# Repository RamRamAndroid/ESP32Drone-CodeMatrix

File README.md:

## Introduction Of CodeMatrix ESP32 Drone

CodeMatrix ESP32 Drone is a compact, WiFi-controlled drone based on the ESP32-S3 microcontroller. Designed for hobbyists, makers, and engineers, CodeMatrix ESP32 Drone offers a simple yet powerful platform for drone experimentation and development. It is an open-hardware project, making it easy to modify and expand.

Whether you’re new to drones or an experienced developer looking to create custom flight applications, LiteWing provides an accessible and affordable way to explore drone technology. Unlike traditional drones that require proprietary controllers, CodeMatrix ESP32 Drone connects to your smartphone, allowing for an intuitive flying experience without additional hardware.

The firmware on CodeMatrix ESP32 Drone supports Crazyflie cfclient and cflib, meaning you can program and control your drone using Python and add more features like height hold, position hold, gesture control, and more.

The latest version includes more GPIO pins, sensor mounts, LED indicators to make it easier to tinker with and program. The PCB frame design keeps it lightweight while reducing costs, making it one of the most affordable DIY drones available.

### Note:- The Files Related To The Drone Are In The Folder Named "Drone"

## Introduction Of CodeMatrix ESP32 Drone Positioning Module

The ESP32 Drone Positioning Module is a plug-and-play optical flow and ToF-based stabilization add-on designed for indoor and GPS-denied flight. Featuring the PMW3901 optical flow sensor for precise X/Y position tracking and the VL53L1X Time-of-Flight sensor for accurate height measurement, this module enables stable height hold and position hold performance. Ideal for DIY drones, autonomous flight experiments, and educational robotics projects.

This module transforms your CodeMatrix ESP32 Drone and Litewing Drone into a fully-equipped autonomous flight platform by adding critical sensor capabilities: precision ToF height measurement, optical motion tracking, and visual status feedback. All connected through a 24-pin connector, eliminating complex wiring while maintaining robust electrical connections suitable for flight operations.

This add-on module is completely compatible with the CodeMatrix ESP32 Drone and LiteWing Drones and consists of the VL53L1x ToF sensor and PMW3901MB optical flow sensor for height hold and position hold, respectively. Apart from this, the module also has 4 Neopixel LEDs that can be programmed to indicate flight status or for visual appeal.

Important: By default, only the ToF sensor, Optical Flow sensor, and Neopixel LEDs will be soldered on the module. The brometric sensor and magnetometer footprint is added only for users who wish to build more using the same board. By default these two sensors will not be populated. The colour of the PCB might also be in black or green color depending on the time of purchase, but features and working will reamin the same.

### Note:- Files Related To The Positioning Module Are In The Folder Named "Module"

## Introduction Of ESP32 Drone Bluetooth Speaker Module (Coming Soon)

The ESP32 Drone Bluetooth Speaker Module is a plug-and-play lightweight Bluetooth speaker system to extend the drone's capabilities beyond flight. By adding a simple Bluetooth audio setup, the drone can now deliver real-time announcements, voice messages, or music directly from the air without requiring any additional coding. The entire system works through a standard Bluetooth connection, making it easy to set up, practical for demonstrations, events, and experimental applications while also being fun.

### Note:- Files Related To The Positioning Module Are In The Folder Named "BluetoothModule"

## Introduction Of ESP32 Drone + Positioning Module PCB

This PCB Has Both The Drone And Module Combined Into One PCB For Easier Manufacturing And Assembly And This Method Is Faster Than Getting The Both Seperatly

### Note:- The Files Related To The Drone + Module PCB Are In The Folder Named "drone+module"

## Add-On Module Template

I Have Made A Template Of The Positioning Module For You To Customize, It Is In The Module Folder

-------------------------------------------------------------------------------------------------------------------------------------------------

### As This Project Is Based On LiteWing, The Instructions Are The Same As Litewing Drone Instructions (https://circuitdigest.com/wiki/litewing/)

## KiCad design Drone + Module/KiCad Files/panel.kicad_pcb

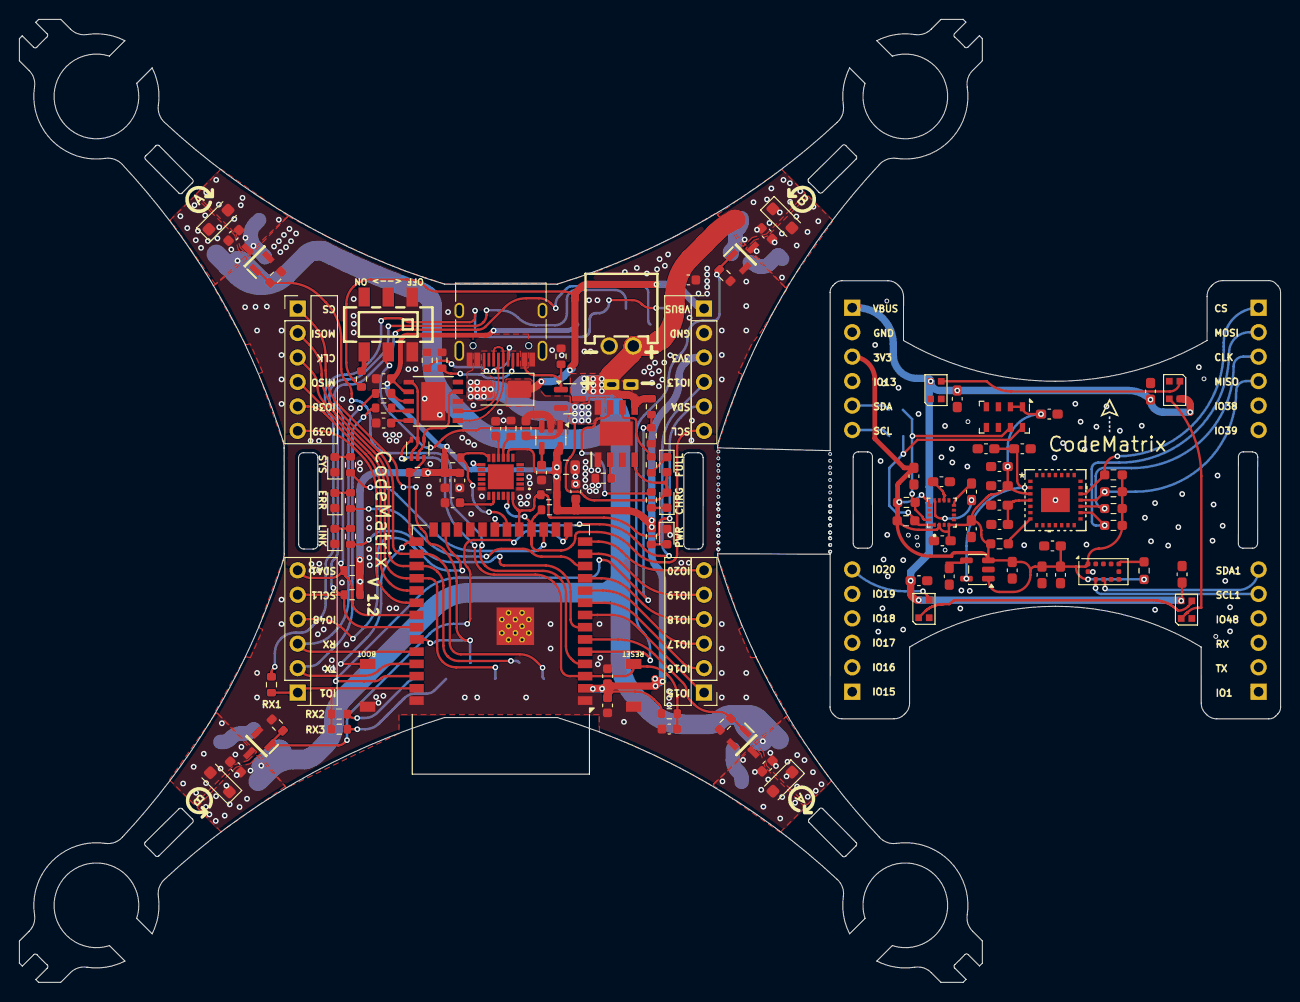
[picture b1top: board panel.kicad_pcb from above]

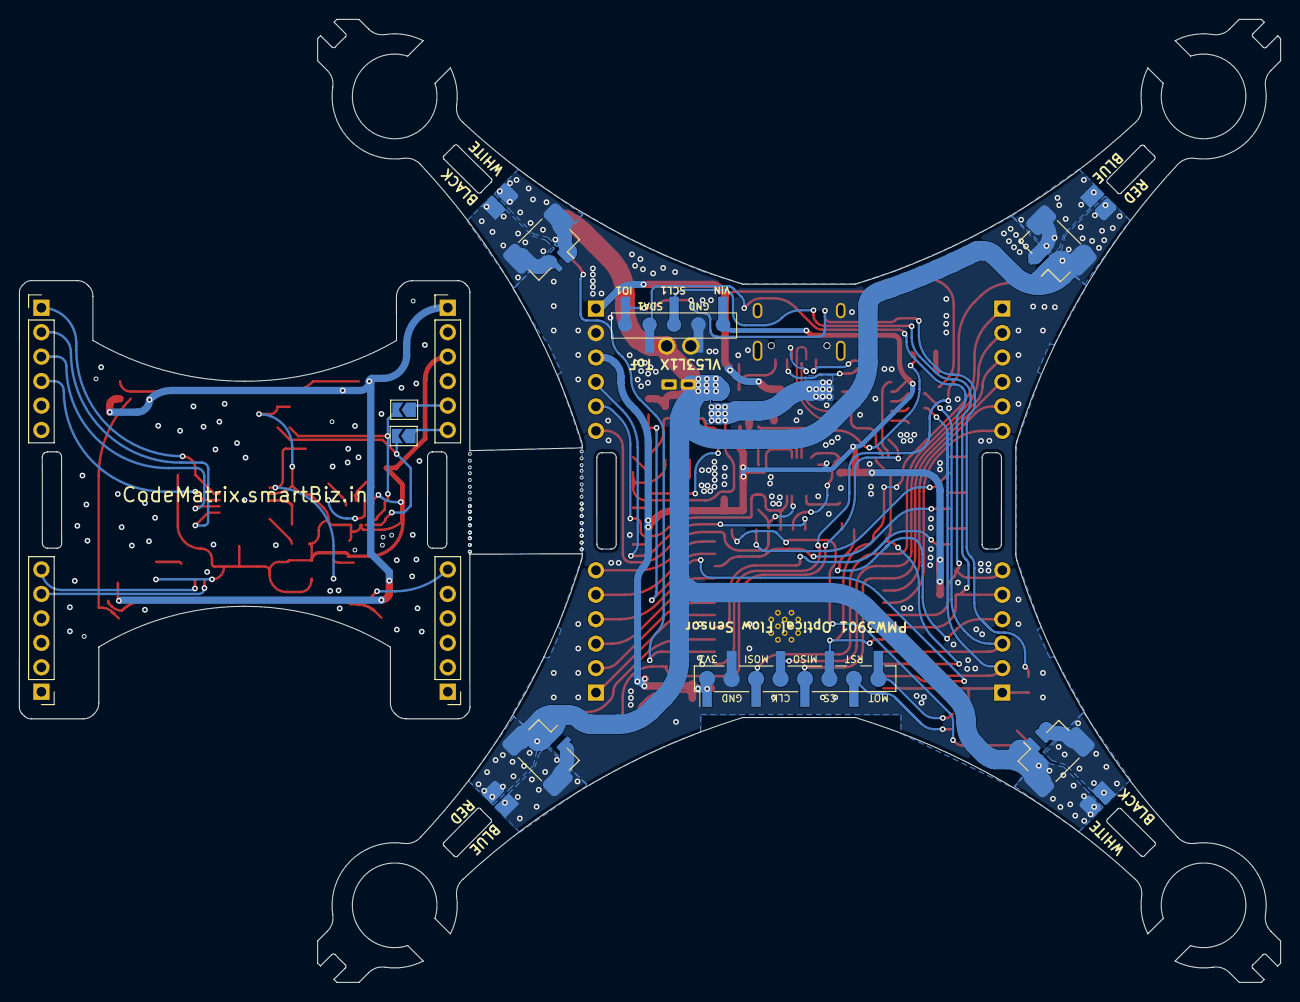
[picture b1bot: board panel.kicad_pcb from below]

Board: 2 copper layers, 131.0 x 100.0 mm, 129 parts (8 on the bottom side), 82 nets.

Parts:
C1, C4, C5#2, C12: 10uF; C_0603_1608Metric
C1#2, C2#2, C3#2, C5: 10uF; C_0603_1608Metric_Pad1.08x0.95mm_HandSolder
C2: 470pF; C_0603_1608Metric
C3: 2.2uF; C_0805_2012Metric
C4#2, C6, C8#2, C10#2, C11, C12#2, C13, C14#2, C15#2: 0.1uF; C_0603_1608Metric_Pad1.08x0.95mm_HandSolder
C6#2, C7#2, C8, C10, C13#2, C14: 100nF; C_0603_1608Metric
C7, C9#2, C16: 4.7uF; C_0603_1608Metric_Pad1.08x0.95mm_HandSolder
C9: 2.2nf; C_0603_1608Metric
C11#2: 10nf; C_0603_1608Metric
C15, C16#2, C17#2, C18#2: 1uF; C_0603_1608Metric
C17: 0.22uF; C_0603_1608Metric_Pad1.08x0.95mm_HandSolder
C18, C19, C20, C21: 1uF; C_0603_1608Metric_Pad1.08x0.95mm_HandSolder
D1, D2#2, D3, D4#2: WS2812B-2020; LED_WS2812B-2020_PLCC4_2.0x2.0mm
D1#2: SS34; D_SMA
D2, D3#2, D4, D5: 1N4148W; D_SOD-123F
IC1: TP4056; SOIC127P600X175-9N
J1: USB_C_Receptacle_USB2.0; USB_C_Receptacle_HRO_TYPE-C-31-M-12
J2: JST XH 2P 2.50mm SMD Hoz; CONN-TH_2P-P2.50_XH-2AW
J3, J3#2, J4, J4#2, J5, J5#2, J6, J6#2: Conn_01x06; PinHeader_1x06_P2.54mm_Vertical
J7, J8, J9, J10: Conn_01x02_Female; LiteWingMotor2
J11: Conn_01x09; PMW3901
J12: Conn_01x06; VL53L1X_BREAKOUT
JP1, JP2: SolderJumper_2_Open; SolderJumper-2_P1.3mm_Open_TrianglePad1.0x1.5mm
LED1, LED2, LED5: LED_Red; LED_0603_1608Metric
LED3, LED6: LED_Blue; LED_0603_1608Metric
LED4: LED_Green; LED_0603_1608Metric
R1, R2: 5.1K; R_0603_1608Metric
R1#2, R8: 4.7K; R_0603_1608Metric_Pad0.98x0.95mm_HandSolder
R2#2, R3, R4, R5#2, R6, R7: 10K; R_0603_1608Metric_Pad0.98x0.95mm_HandSolder
R3#2, R8#2, R26, R27: 100K; R_0603_1608Metric
R4#2: 470R; R_0603_1608Metric
R5: 1.2K; R_0603_1608Metric
R6#2, R7#2, R9, R10, R11, R12, R13: 1K; R_0603_1608Metric
R14, R16, R17, R18, R19, R20, R21, R22, R23, R24, R25: 10k; R_0603_1608Metric
R15: 4.7k; R_0603_1608Metric
R28, R29, R30: 0R; R_0603_1608Metric
SW1: MST22D18G2_125; SW-SMD_MST22D18G2
SW2, SW3: Tactile Switch 3x4x2; Tactile 3x4x2mm TS-A010
T1, T2, T3, T4: IRLML6344TRPBF; SOT95P237X112-3N
U1: AO3401A; SOT-23
U1#2: SPX3819M5-L-1-8; SOT-23-5
U2: PMW3901MB-TXQT; QFN_01MB-TXQT_PIX
U2#2: SPX3819M5-L-3-3/TR; SOT-23-5
U3: VL53L1CXV0FY1; ST_VL53L1x
U4: MS5611-01BA; LGA-8_3x5mm_P1.25mm
U5: HMC5883L-TR; XDCR_HMC5883L-TR
U5#2: CH340K; ESSOP-10_3.9x4.9mm_P1.00mm
U6: 2N27002DW; SOT-363_SC-70-6
U7: MPU-6050; MPU6050
U8: ESP32-S3-WROOM-1

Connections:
+2V0: C3#2.1, C4#2.1, U1#2.5 (OUT), U2.2 (VDD)
+3V3: C3.1, C4.1, C7#2.1, C10.1, C11#2.1, C12.1, C13#2.1, J4.3, J11.1, J12.1, R4#2.2, R14.2, R16.2, R17.2, R18.2, R19.2, R20.2, R21.2, U2#2.5 (OUT), U5#2.7 (VCC), U7.8 (VLOGIC), U7.13 (VDD), U8.2 (3V3)
+5V: D1#2.2 (A), IC1.4 (VCC), IC1.8 (CE), J1.A4 (VBUS), J1.A9 (VBUS), J1.B4 (VBUS), J1.B9 (VBUS), LED2.2 (A), LED3.2 (A), R3#2.1, U1.1 (G)
+BATT: C5#2.1, C15.1, C16#2.1, C17#2.1, C18#2.1, D2.1 (K), D3#2.1 (K), D4.1 (K), D5.1 (K), IC1.5 (BAT), J2.1, J7.1, J8.1, J9.1, J10.1, R26.1, U1.3 (D)
/ADC_BAT: R26.2, R27.1, U8.38 (IO2)
/BUZ1: J6.5, J6#2.5, U8.31 (IO38)
/BUZ2: J6.6, J6#2.6, U8.32 (IO39)
/CLK: J6.3, J6#2.3, J11.4, R5#2.1, U2.17 (SCLK), U8.29 (IO36)
/CS: J6.1, J6#2.1, J11.6, R3.1, U2.19 (NCS), U8.35 (IO42)
/D+: J1.A6 (D+), J1.B6 (D+), U5#2.1 (D+)
/D-: J1.A7 (D-), J1.B7 (D-), U5#2.2 (D-)
/DTR: U5#2.4 (DTR), U6.2, U6.4
/EN: C14.1, R18.1, SW3.2, U6.6, U8.3 (EN)
/IO0: R19.1, SW2.2, U6.3, U8.27 (IO0)
/IO1: J5.1, J5#2.1, R28.1, R29.1, R30.1, U8.39 (IO1)
/IO13: J4.4, J4#2.4, U8.21 (IO13)
/IO15: J3.1, J3#2.1, U8.8 (IO15)
/IO16: J3.2, J3#2.2, U8.9 (IO16)
/IO17: J3.3, J3#2.3, U8.10 (IO17)
/IO18: J3.4, J3#2.4, U8.11 (IO18)
/IO19: J3.5, J3#2.5, U8.13 (IO19)
/IO20: D1.3 (DIN), J3.6, J3#2.6, U8.14 (IO20)
/IO48: J5.4, U8.25 (IO48)
/LDO_H: R8#2.2, SW1.3
/LED_BLUE: R13.2, U8.7 (IO7)
/LED_GREEN: R11.2, U8.17 (IO9)
/LED_RED: R12.2, U8.12 (IO8)
/MISO: J6.4, J6#2.4, J11.5, R4.1, U2.18 (MISO), U8.30 (IO37)
/MOSI: J6.2, J6#2.2, J11.3, R6.1, U2.16 (MOSI), U8.28 (IO35)
/MOT_1: R22.2, T1.1 (G), U8.5 (IO5)
/MOT_2: R23.2, T2.1 (G), U8.6 (IO6)
/MOT_3: R24.2, T3.1 (G), U8.15 (IO3)
/MOT_4: R25.2, T4.1 (G), U8.4 (IO4)
/MPU_INT: R17.1, U7.12 (INT), U8.20 (IO12)
/RTS: U5#2.6 (RTS), U6.1, U6.5
/RX: J5.3, J5#2.3, R10.1, U8.36 (RXD0)
/SCL: J4.6, JP2.2 (B), R8.1, R16.1, U4.8 (SCLK), U5.1 (SCL), U7.23 (SCL), U8.18 (IO10)
/SCL1: J5.5, J5#2.5, J12.3, R21.1, U3.10 (SCL), U8.34 (IO41)
/SDA: J4.5, JP1.2 (B), R1#2.1, R14.1, U4.7 (SDI/SDA), U5.16 (SDA), U7.24 (SDA), U8.19 (IO11)
/SDA1: J5.6, J5#2.6, J12.4, R20.1, U3.9 (SDA), U8.33 (IO40)
/TX: J5.2, J5#2.2, R9.1, U8.37 (TXD0)
GND: C1.2, C1#2.2, C2.2, C2#2.2, C3.2, C3#2.2, C4.2, C4#2.2, C5.2, C5#2.2, C6.2, C6#2.1, C7.2, C7#2.2, C8.2, C8#2.2, C9.2, C9#2.2, C10.2, C10#2.2, C11.2, C11#2.2, C12.2, C12#2.1, C13.1, C13#2.2, C14.2, C14#2.1, C15#2.1, C16.1, C18.2, C19.2, C20.2, C21.2, D1.2 (VSS), D2#2.2 (VSS), D3.2 (VSS), D4#2.2 (VSS), IC1.1 (TEMP), IC1.3 (GND), IC1.9 (EP), J1.A1 (GND), J1.A12 (GND), J1.B1 (GND), J1.B12 (GND), J1.S1 (SHIELD), J2.2, J4.2, J4#2.2, J5#2.4, J11.2, J12.2, LED1.1 (K), LED4.1 (K), LED5.1 (K), LED6.1 (K), R1.2, R2.2, R3#2.2, R5.2, R15.1, R22.1, R23.1, R24.1, R25.1, R27.2, SW1.1, SW1.4, SW2.1, SW3.1, T1.2 (S), T2.2 (S), T3.2 (S), T4.2 (S), U1#2.2 (GND), U2.1 (GND), U2.21 (GND), U2.29 (GND), U2#2.2 (GND), U3.2 (AVSSVCSEL), U3.3 (GND), U3.4 (GND), U3.6 (GND), U3.12 (GND), U4.3 (GND), U4.4 (CSB), U4.5 (CSB), U5.9 (GND), U5.11 (GND), U5#2.3 (GND), U5#2.11 (EP), U7.1 (CLKIN), U7.11 (FSYNC), U7.18 (GND), U8.1 (GND), U8.40 (GND), U8.41 (GND)
LDO_EN: SW1.2, U2#2.3 (EN)
unnamed: D1.1 (DOUT), D2#2.3 (DIN)
unnamed: C15.2, D2.2 (A), J7.2, T1.3 (D)
unnamed: D2#2.1 (DOUT), D3.3 (DIN)
unnamed: C16#2.2, D3#2.2 (A), J8.2, T2.3 (D)
unnamed: D3.1 (DOUT), D4#2.3 (DIN)
unnamed: C17#2.2, D4.2 (A), J9.2, T3.3 (D)
unnamed: C18#2.2, D5.2 (A), J10.2, T4.3 (D)
unnamed: IC1.2 (PROG), R5.1
unnamed: IC1.7 (~CHRG), R6#2.2
unnamed: IC1.6 (~STDBY), R7#2.2
unnamed: J1.A5 (CC1), R2.1
unnamed: J1.B5 (CC2), R1.1
unnamed: J4#2.5, JP1.1 (A)
unnamed: J4#2.6, JP2.1 (A)
unnamed: J11.7, R29.2
unnamed: J11.8, R30.2
unnamed: J12.5, R28.2
unnamed: LED1.2 (A), R4#2.1
unnamed: LED2.1 (K), R6#2.1
unnamed: LED3.1 (K), R7#2.1
unnamed: LED4.2 (A), R11.1
unnamed: LED5.2 (A), R12.1
unnamed: LED6.2 (A), R13.1
unnamed: C2#2.1, U1#2.4 (BP)
unnamed: C2.1, U2#2.4 (BP)
unnamed: R2#2.2, U2.7 (NRESET)
unnamed: C7.1, C8#2.1, U2.4 (VREG)
unnamed: R7.2, U3.5 (XSHUT)
unnamed: C16.2, U5.10 (C1)
unnamed: R9.2, U5#2.9 (RXD)
unnamed: C17.2, U5.12 (SETC)
unnamed: C17.1, U5.8 (SETP)
unnamed: R10.2, U5#2.8 (TXD)
unnamed: C6#2.2, U5#2.10 (V3)
unnamed: R15.2, U7.9 (AD0)
unnamed: C9.1, U7.20 (CPOUT)
unnamed: C8.1, U7.10 (REGOUT)
VBUS: C1.1, C18.1, C19.1, C20.1, C21.1, D1.4 (VDD), D1#2.1 (K), D2#2.4 (VDD), D3.4 (VDD), D4#2.4 (VDD), J4.1, J4#2.1, R8#2.1, U1.2 (S), U2#2.1 (IN)
VDD: C1#2.1, C5.1, C6.1, C9#2.1, C10#2.1, C11.1, C12#2.2, C13.2, C14#2.2, C15#2.2, J4#2.3, R1#2.2, R2#2.1, R3.2, R4.2, R5#2.2, R6.2, R7.1, R8.2, U1#2.1 (IN), U1#2.3 (EN), U2.3 (VDDIO), U3.1 (AVDDVCSEL), U3.11 (AVDD), U4.1 (VDD), U4.2 (PS), U5.2 (VDD), U5.4 (S1), U5.13 (VDDIO)

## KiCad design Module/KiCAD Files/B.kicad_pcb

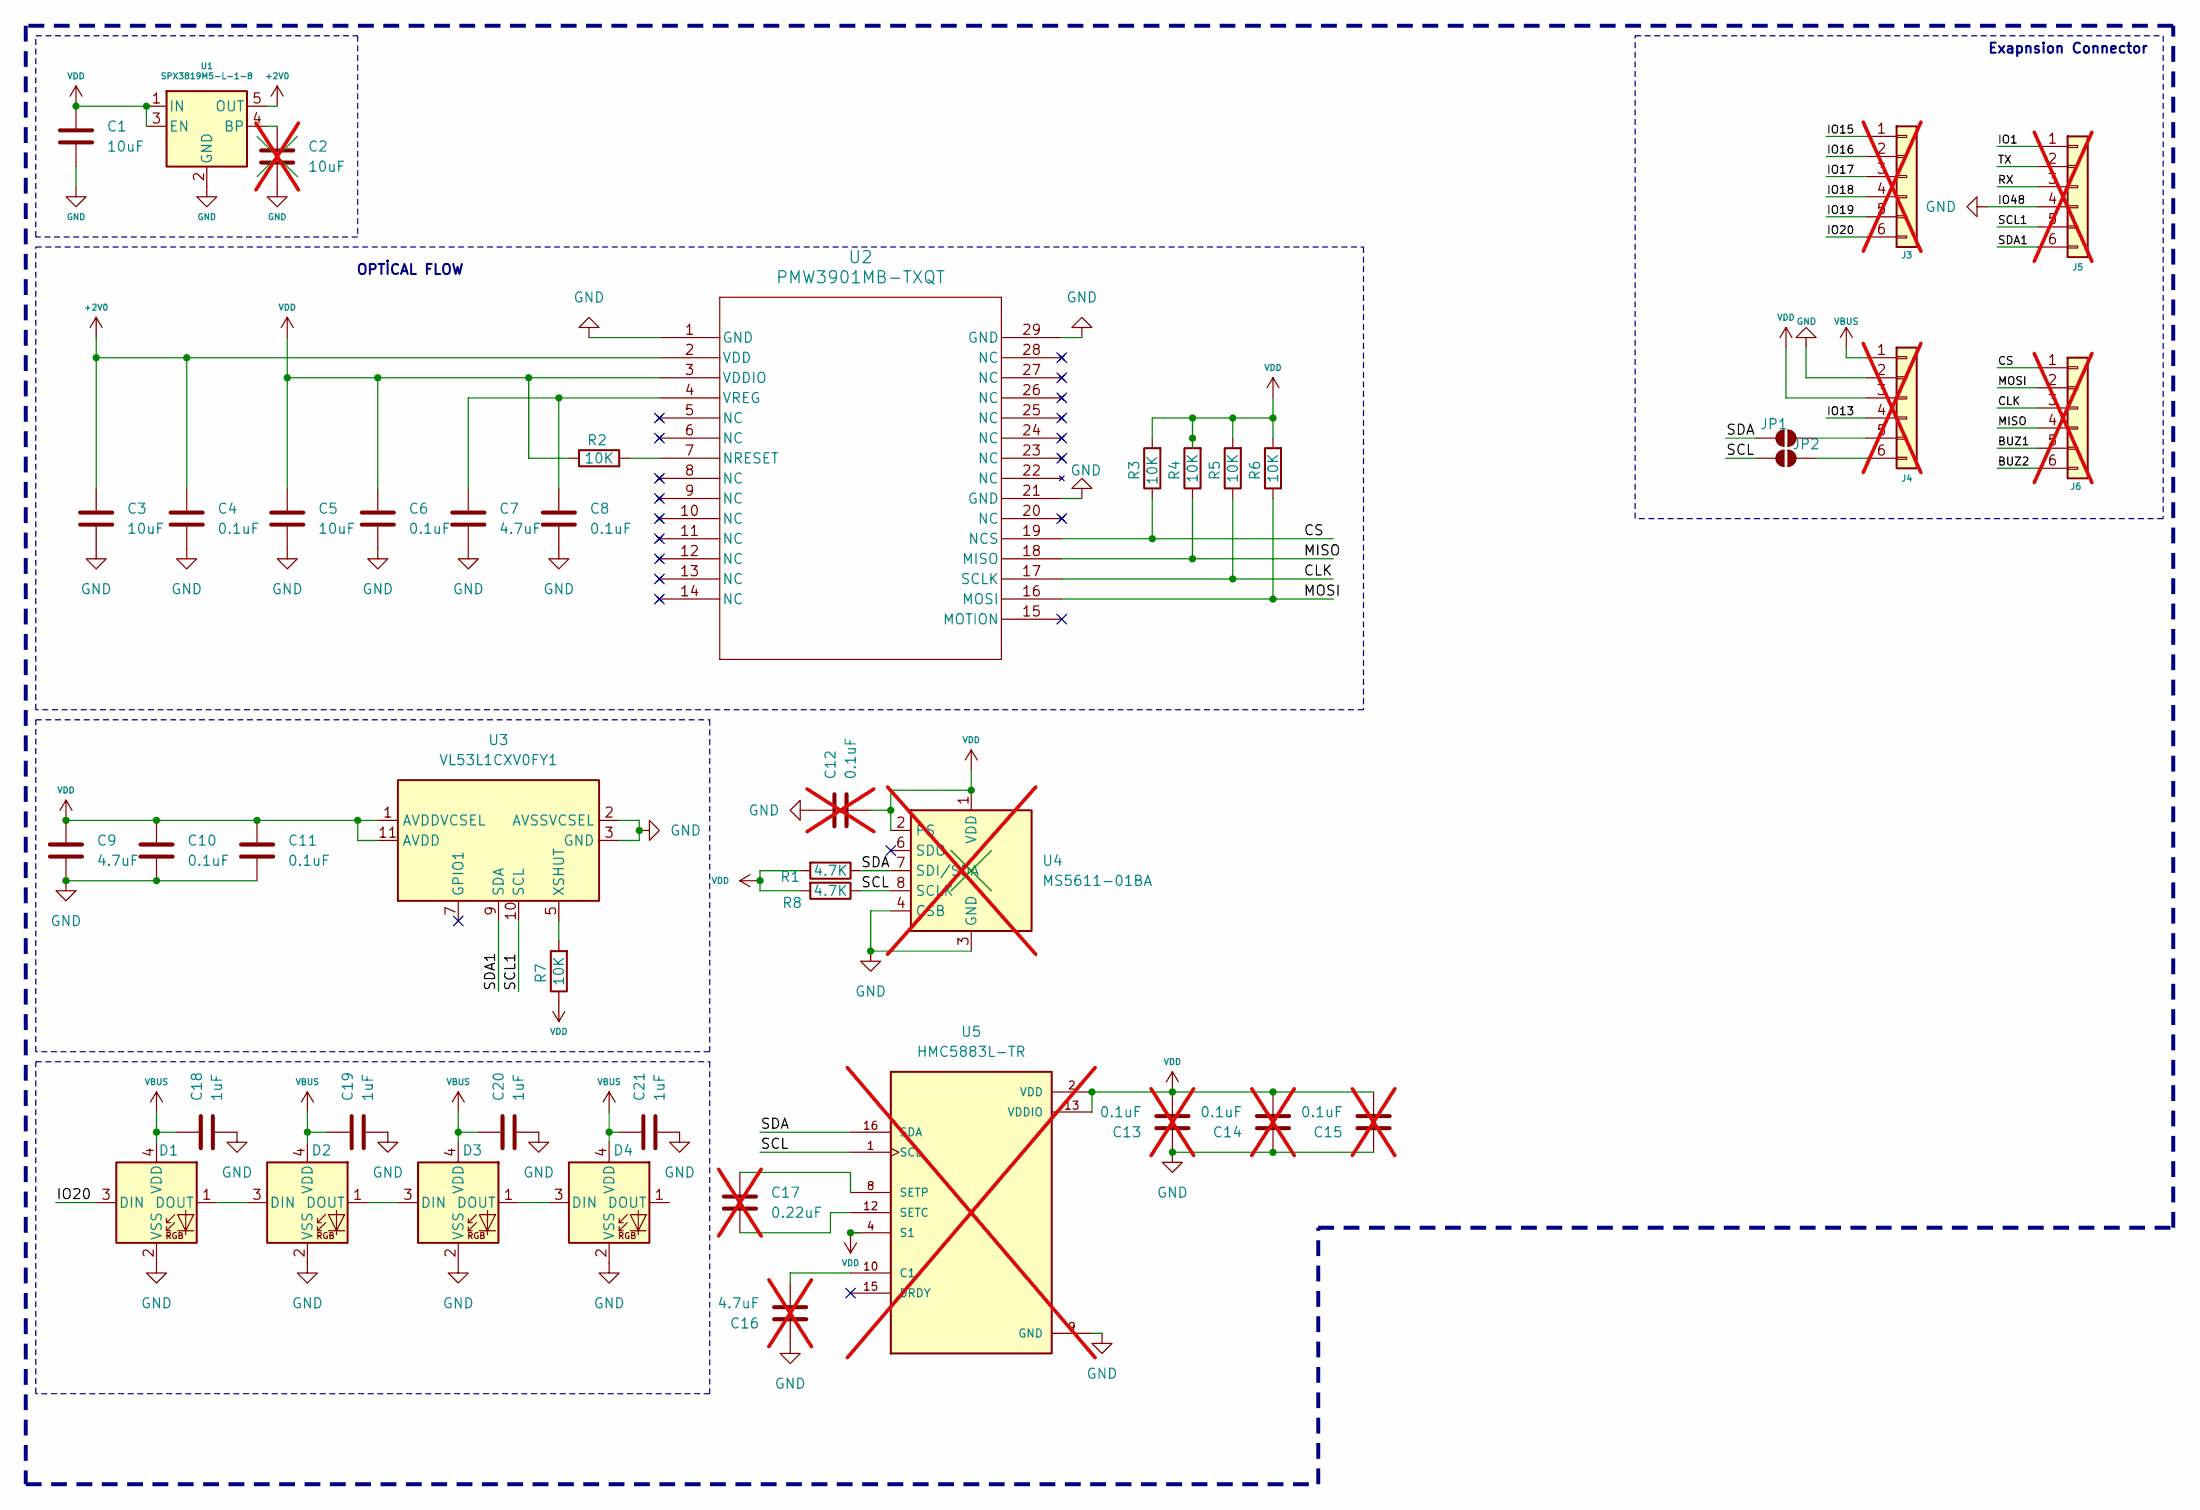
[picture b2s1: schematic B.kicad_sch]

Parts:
C1, C3, C5: 10uF; C_0603_1608Metric_Pad1.08x0.95mm_HandSolder
C2: 10uF; C_0603_1608Metric_Pad1.08x0.95mm_HandSolder; not fitted
C4, C6, C8, C10, C11: 0.1uF; C_0603_1608Metric_Pad1.08x0.95mm_HandSolder
C7, C9: 4.7uF; C_0603_1608Metric_Pad1.08x0.95mm_HandSolder
C12, C13, C14, C15: 0.1uF; C_0603_1608Metric_Pad1.08x0.95mm_HandSolder; not fitted
C16: 4.7uF; C_0603_1608Metric_Pad1.08x0.95mm_HandSolder; not fitted
C17: 0.22uF; C_0603_1608Metric_Pad1.08x0.95mm_HandSolder; not fitted
C18, C19, C20, C21: 1uF; C_0603_1608Metric_Pad1.08x0.95mm_HandSolder
D1, D2, D3, D4: WS2812B-2020; LED_WS2812B-2020_PLCC4_2.0x2.0mm
J3, J4, J5, J6: Conn_01x06; PinHeader_1x06_P2.54mm_Vertical; not fitted
JP1, JP2: SolderJumper_2_Open; SolderJumper-2_P1.3mm_Open_TrianglePad1.0x1.5mm
R1, R8: 4.7K; R_0603_1608Metric_Pad0.98x0.95mm_HandSolder
R2, R3, R4, R5, R6, R7: 10K; R_0603_1608Metric_Pad0.98x0.95mm_HandSolder
U1: SPX3819M5-L-1-8; SOT-23-5
U2: PMW3901MB-TXQT; QFN_01MB-TXQT_PIX
U3: VL53L1CXV0FY1; ST_VL53L1x
U4: MS5611-01BA; LGA-8_3x5mm_P1.25mm; not fitted
U5: HMC5883L-TR; XDCR_HMC5883L-TR; PARTREV E; not fitted

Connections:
+2V0: C3.1, C4.1, U1.5 (OUT), U2.2 (VDD)
/BUZ1: J6.5
/BUZ2: J6.6
/CLK: J6.3, R5.1, U2.17 (SCLK)
/CS: J6.1, R3.1, U2.19 (NCS)
/IO1: J5.1
/IO13: J4.4
/IO15: J3.1
/IO16: J3.2
/IO17: J3.3
/IO18: J3.4
/IO19: J3.5
/IO20: D1.3 (DIN), J3.6
/MISO: J6.4, R4.1, U2.18 (MISO)
/MOSI: J6.2, R6.1, U2.16 (MOSI)
/RX: J5.3
/SCL: JP2.2 (B), R8.1, U4.8 (SCLK), U5.1 (SCL)
/SCL1: J5.5, U3.10 (SCL)
/SDA: JP1.2 (B), R1.1, U4.7 (SDI/SDA), U5.16 (SDA)
/SDA1: J5.6, U3.9 (SDA)
/TX: J5.2
GND: C1.2, C2.2, C3.2, C4.2, C5.2, C6.2, C7.2, C8.2, C9.2, C10.2, C11.2, C12.1, C13.1, C14.1, C15.1, C16.1, C18.2, C19.2, C20.2, C21.2, D1.2 (VSS), D2.2 (VSS), D3.2 (VSS), D4.2 (VSS), J4.2, J5.4, U1.2 (GND), U2.1 (GND), U2.21 (GND), U2.29 (GND), U3.2 (AVSSVCSEL), U3.3 (GND), U3.4 (GND), U3.6 (GND), U3.12 (GND), U4.3 (GND), U4.4 (CSB), U4.5 (CSB), U5.9 (GND), U5.11 (GND)
unnamed: D1.1 (DOUT), D2.3 (DIN)
unnamed: D2.1 (DOUT), D3.3 (DIN)
unnamed: D3.1 (DOUT), D4.3 (DIN)
unnamed: J4.5, JP1.1 (A)
unnamed: J4.6, JP2.1 (A)
unnamed: C2.1, U1.4 (BP)
unnamed: R2.2, U2.7 (NRESET)
unnamed: C7.1, C8.1, U2.4 (VREG)
unnamed: R7.2, U3.5 (XSHUT)
unnamed: C16.2, U5.10 (C1)
unnamed: C17.2, U5.12 (SETC)
unnamed: C17.1, U5.8 (SETP)
VBUS: C18.1, C19.1, C20.1, C21.1, D1.4 (VDD), D2.4 (VDD), D3.4 (VDD), D4.4 (VDD), J4.1
VDD: C1.1, C5.1, C6.1, C9.1, C10.1, C11.1, C12.2, C13.2, C14.2, C15.2, J4.3, R1.2, R2.1, R3.2, R4.2, R5.2, R6.2, R7.1, R8.2, U1.1 (IN), U1.3 (EN), U2.3 (VDDIO), U3.1 (AVDDVCSEL), U3.11 (AVDD), U4.1 (VDD), U4.2 (PS), U5.2 (VDD), U5.4 (S1), U5.13 (VDDIO)

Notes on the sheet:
OPTİCAL FLOW
Exapnsion Connector

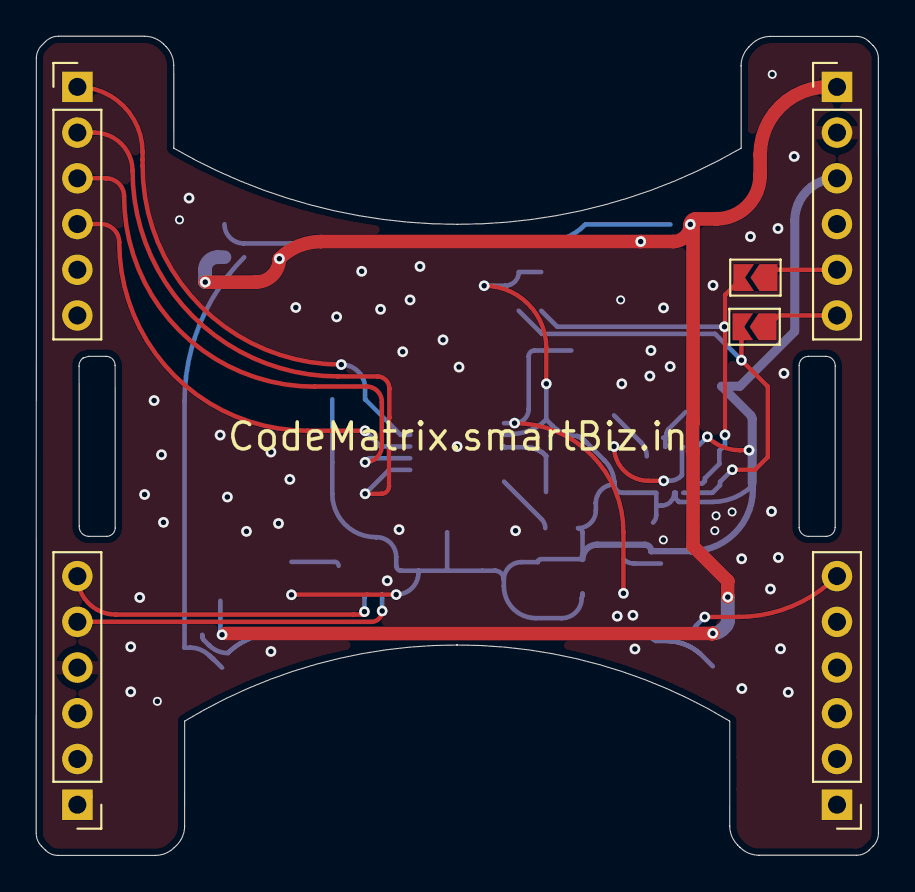
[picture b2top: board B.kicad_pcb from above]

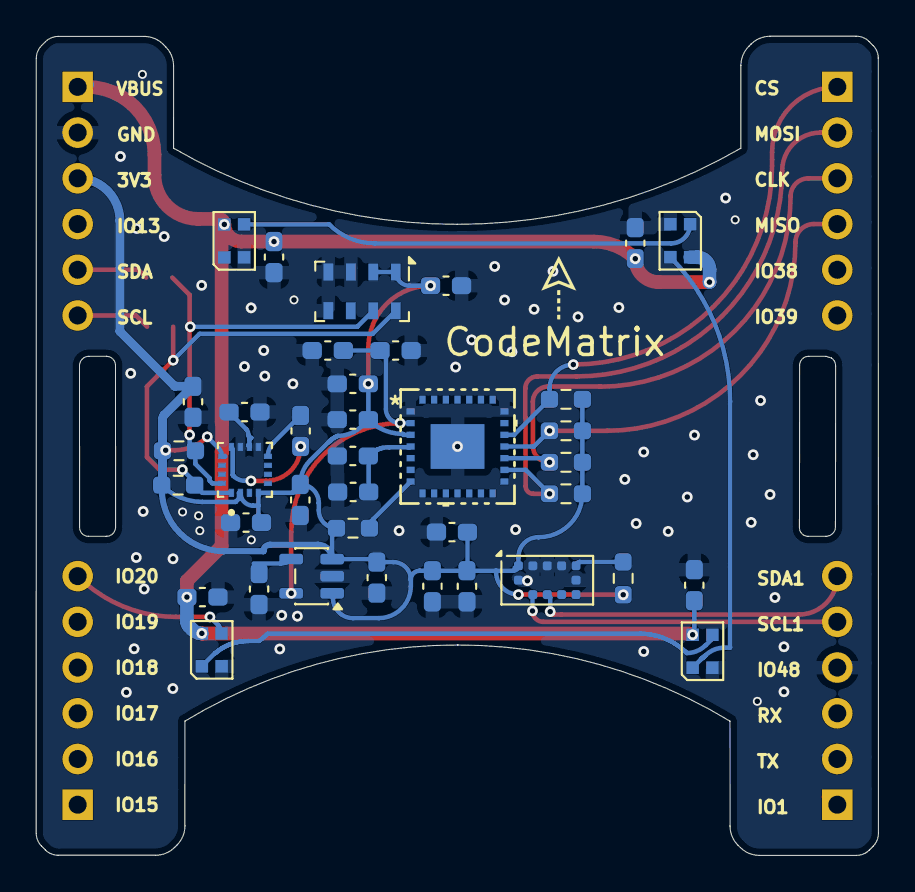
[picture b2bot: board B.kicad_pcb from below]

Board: 2 copper layers, 46.8 x 45.5 mm, 44 parts (38 on the bottom side), 25 nets.

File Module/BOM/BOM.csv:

"Id";"Designator";"Footprint";"Quantity";"Designation";"Supplier and ref";
1;"C1, C3, C5";"C_0603_1608Metric_Pad1.08x0.95mm_HandSolder";3;"10uF";;;
2;"C4, C6, C8, C10, C11";"C_0603_1608Metric_Pad1.08x0.95mm_HandSolder";5;"0.1uF";;;
3;"C7, C9";"C_0603_1608Metric_Pad1.08x0.95mm_HandSolder";2;"4.7uF";;;
4;"C18, C19, C20, C21";"C_0603_1608Metric_Pad1.08x0.95mm_HandSolder";4;"1uF";;;
5;"D1, D2, D3, D4";"LED_WS2812B-2020_PLCC4_2.0x2.0mm";4;"WS2812B-2020";;;
6;"R1, R8";"R_0603_1608Metric_Pad0.98x0.95mm_HandSolder";2;"4.7K";;;
7;"R2, R3, R4, R5, R6, R7";"R_0603_1608Metric_Pad0.98x0.95mm_HandSolder";6;"10K";;;
8;"U1";"SOT-23-5";1;"SPX3819M5-L-1-8";;;
9;"U2";"QFN_01MB-TXQT_PIX";1;"PMW3901MB-TXQT";;;
10;"U3";"ST_VL53L1x";1;"VL53L1CXV0FY1";;;

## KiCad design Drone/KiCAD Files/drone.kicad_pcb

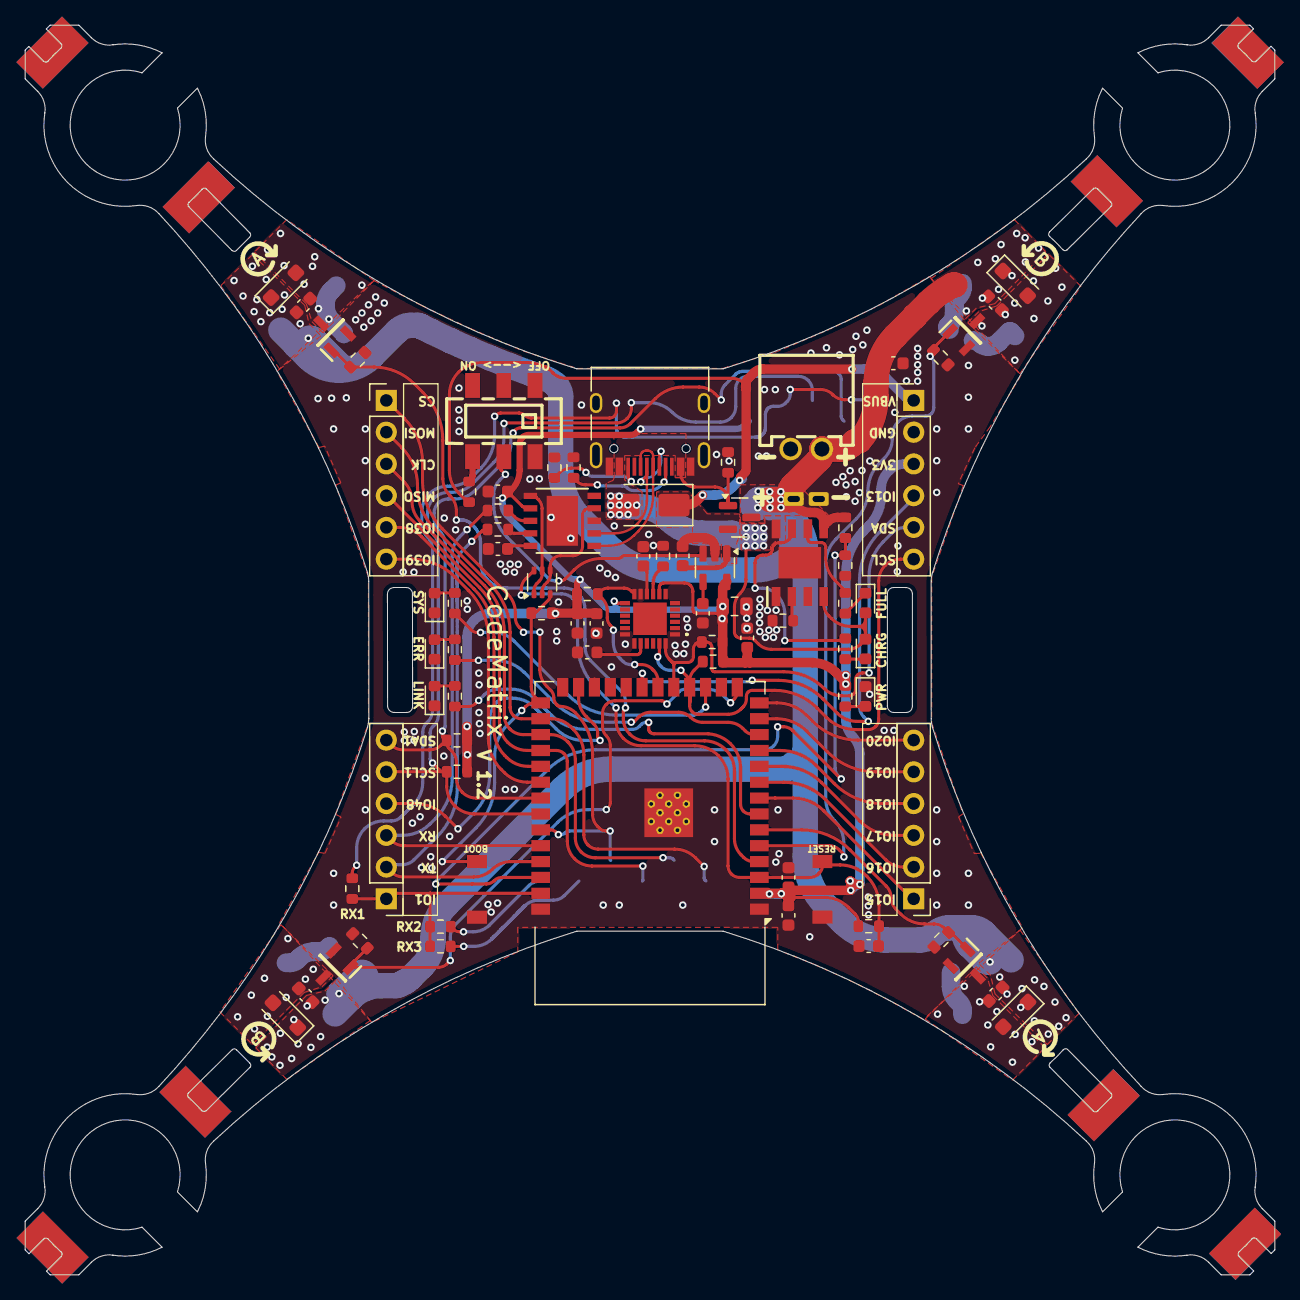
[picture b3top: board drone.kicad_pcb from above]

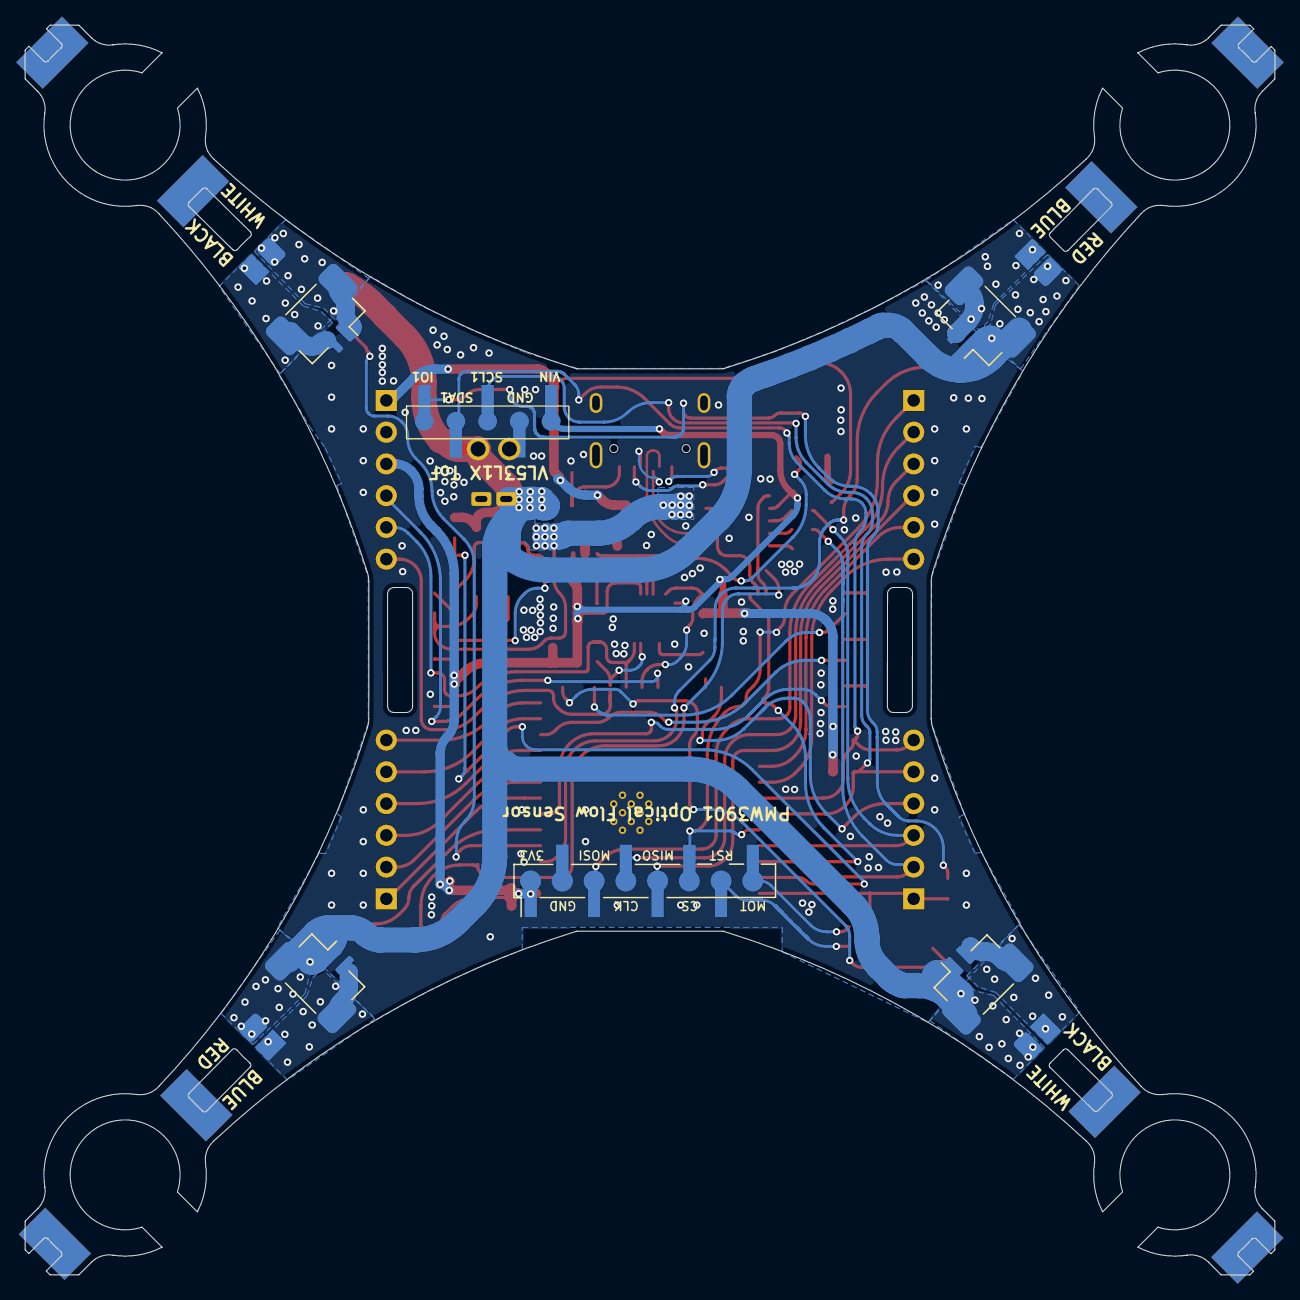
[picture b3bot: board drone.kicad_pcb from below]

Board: 2 copper layers, 100.0 x 100.0 mm, 85 parts (2 on the bottom side), 68 nets.

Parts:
C1, C4, C5, C12: 10uF; C_0603_1608Metric
C2: 470pF; C_0603_1608Metric
C3: 2.2uF; C_0805_2012Metric
C6, C7, C8, C10, C13, C14: 100nF; C_0603_1608Metric
C9: 2.2nf; C_0603_1608Metric
C11: 10nf; C_0603_1608Metric
C15, C16, C17, C18: 1uF; C_0603_1608Metric
D1: SS34; D_SMA
D2, D3, D4, D5: 1N4148W; D_SOD-123F
IC1: TP4056; SOIC127P600X175-9N
J1: USB_C_Receptacle_USB2.0; USB_C_Receptacle_HRO_TYPE-C-31-M-12
J2: JST XH 2P 2.50mm SMD Hoz; CONN-TH_2P-P2.50_XH-2AW
J3, J4, J5, J6: Conn_01x06; PinHeader_1x06_P2.54mm_Vertical
J7, J8, J9, J10: Conn_01x02_Female; LiteWingMotor2
J11: Conn_01x09; PMW3901
J12: Conn_01x06; VL53L1X_BREAKOUT
LED1, LED2, LED5: LED_Red; LED_0603_1608Metric
LED3, LED6: LED_Blue; LED_0603_1608Metric
LED4: LED_Green; LED_0603_1608Metric
R1, R2: 5.1K; R_0603_1608Metric
R3, R8, R26, R27: 100K; R_0603_1608Metric
R4: 470R; R_0603_1608Metric
R5: 1.2K; R_0603_1608Metric
R6, R7, R9, R10, R11, R12, R13: 1K; R_0603_1608Metric
R14, R16, R17, R18, R19, R20, R21, R22, R23, R24, R25: 10k; R_0603_1608Metric
R15: 4.7k; R_0603_1608Metric
R28, R29, R30: 0R; R_0603_1608Metric
SW1: MST22D18G2_125; SW-SMD_MST22D18G2
SW2, SW3: Tactile Switch 3x4x2; Tactile 3x4x2mm TS-A010
T1, T2, T3, T4: IRLML6344TRPBF; SOT95P237X112-3N
U1: AO3401A; SOT-23
U2: SPX3819M5-L-3-3/TR; SOT-23-5
U5: CH340K; ESSOP-10_3.9x4.9mm_P1.00mm
U6: 2N27002DW; SOT-363_SC-70-6
U7: MPU-6050; MPU6050
U8: ESP32-S3-WROOM-1

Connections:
+3V3: C3.1, C4.1, C7.1, C10.1, C11.1, C12.1, C13.1, J4.3, J11.1, J12.1, R4.2, R14.2, R16.2, R17.2, R18.2, R19.2, R20.2, R21.2, U2.5 (OUT), U5.7 (VCC), U7.8 (VLOGIC), U7.13 (VDD), U8.2 (3V3)
+5V: D1.2 (A), IC1.4 (VCC), IC1.8 (CE), J1.A4 (VBUS), J1.A9 (VBUS), J1.B4 (VBUS), J1.B9 (VBUS), LED2.2 (A), LED3.2 (A), R3.1, U1.1 (G)
+BATT: C5.1, C15.1, C16.1, C17.1, C18.1, D2.1 (K), D3.1 (K), D4.1 (K), D5.1 (K), IC1.5 (BAT), J2.1, J7.1, J8.1, J9.1, J10.1, R26.1, U1.3 (D)
/ADC_BAT: R26.2, R27.1, U8.38 (IO2)
/BUZ1: J6.5, U8.31 (IO38)
/BUZ2: J6.6, U8.32 (IO39)
/CLK: J6.3, J11.4, U8.29 (IO36)
/CS: J6.1, J11.6, U8.35 (IO42)
/D+: J1.A6 (D+), J1.B6 (D+), U5.1 (D+)
/D-: J1.A7 (D-), J1.B7 (D-), U5.2 (D-)
/DTR: U5.4 (DTR), U6.2, U6.4
/EN: C14.1, R18.1, SW3.2, U6.6, U8.3 (EN)
/IO0: R19.1, SW2.2, U6.3, U8.27 (IO0)
/IO1: J5.1, R28.1, R29.1, R30.1, U8.39 (IO1)
/IO13: J4.4, U8.21 (IO13)
/IO15: J3.1, U8.8 (IO15)
/IO16: J3.2, U8.9 (IO16)
/IO17: J3.3, U8.10 (IO17)
/IO18: J3.4, U8.11 (IO18)
/IO19: J3.5, U8.13 (IO19)
/IO20: J3.6, U8.14 (IO20)
/IO48: J5.4, U8.25 (IO48)
/LDO_H: R8.2, SW1.3
/LED_BLUE: R13.2, U8.7 (IO7)
/LED_GREEN: R11.2, U8.17 (IO9)
/LED_RED: R12.2, U8.12 (IO8)
/MISO: J6.4, J11.5, U8.30 (IO37)
/MOSI: J6.2, J11.3, U8.28 (IO35)
/MOT_1: R22.2, T1.1 (G), U8.5 (IO5)
/MOT_2: R23.2, T2.1 (G), U8.6 (IO6)
/MOT_3: R24.2, T3.1 (G), U8.15 (IO3)
/MOT_4: R25.2, T4.1 (G), U8.4 (IO4)
/MPU_INT: R17.1, U7.12 (INT), U8.20 (IO12)
/RTS: U5.6 (RTS), U6.1, U6.5
/RX: J5.3, R10.1, U8.36 (RXD0)
/SCL: J4.6, R16.1, U7.23 (SCL), U8.18 (IO10)
/SCL1: J5.5, J12.3, R21.1, U8.34 (IO41)
/SDA: J4.5, R14.1, U7.24 (SDA), U8.19 (IO11)
/SDA1: J5.6, J12.4, R20.1, U8.33 (IO40)
/TX: J5.2, R9.1, U8.37 (TXD0)
GND: C1.2, C2.2, C3.2, C4.2, C5.2, C6.1, C7.2, C8.2, C9.2, C10.2, C11.2, C12.2, C13.2, C14.2, IC1.1 (TEMP), IC1.3 (GND), IC1.9 (EP), J1.A1 (GND), J1.A12 (GND), J1.B1 (GND), J1.B12 (GND), J1.S1 (SHIELD), J2.2, J4.2, J11.2, J12.2, LED1.1 (K), LED4.1 (K), LED5.1 (K), LED6.1 (K), R1.2, R2.2, R3.2, R5.2, R15.1, R22.1, R23.1, R24.1, R25.1, R27.2, SW1.1, SW1.4, SW2.1, SW3.1, T1.2 (S), T2.2 (S), T3.2 (S), T4.2 (S), U2.2 (GND), U5.3 (GND), U5.11 (EP), U7.1 (CLKIN), U7.11 (FSYNC), U7.18 (GND), U8.1 (GND), U8.40 (GND), U8.41 (GND)
LDO_EN: SW1.2, U2.3 (EN)
unnamed: C15.2, D2.2 (A), J7.2, T1.3 (D)
unnamed: C16.2, D3.2 (A), J8.2, T2.3 (D)
unnamed: C17.2, D4.2 (A), J9.2, T3.3 (D)
unnamed: C18.2, D5.2 (A), J10.2, T4.3 (D)
unnamed: IC1.2 (PROG), R5.1
unnamed: IC1.7 (~CHRG), R6.2
unnamed: IC1.6 (~STDBY), R7.2
unnamed: J1.A5 (CC1), R2.1
unnamed: J1.B5 (CC2), R1.1
unnamed: J11.7, R29.2
unnamed: J11.8, R30.2
unnamed: J12.5, R28.2
unnamed: LED1.2 (A), R4.1
unnamed: LED2.1 (K), R6.1
unnamed: LED3.1 (K), R7.1
unnamed: LED4.2 (A), R11.1
unnamed: LED5.2 (A), R12.1
unnamed: LED6.2 (A), R13.1
unnamed: C2.1, U2.4 (BP)
unnamed: R9.2, U5.9 (RXD)
unnamed: R10.2, U5.8 (TXD)
unnamed: C6.2, U5.10 (V3)
unnamed: R15.2, U7.9 (AD0)
unnamed: C9.1, U7.20 (CPOUT)
unnamed: C8.1, U7.10 (REGOUT)
VBUS: C1.1, D1.1 (K), J4.1, R8.1, U1.2 (S), U2.1 (IN)
